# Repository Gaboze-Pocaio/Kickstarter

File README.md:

# Game Boy Zero

> Looking for a no frills multi system emulator that fits in your pocket? Look no further! This is it, Gameboy Zero - Handheld Edition!!!
>
> This project is a collaboration between  [moosepr](https://github.com/moosepr/) and  [32teeth](https://github.com/32teeth)
>
> We are **live** on [KickStarter](https://www.kickstarter.com/projects/sparky/gameboy-zero-handheld-edition)
>
> **Thank you everyone for your support.**

## Introduction

### Gameboy Zero - Handheld Edition

Raspberry Pi Zero based arcade in you pocket

### Features:

* 2.8" TFT LCD
* Gameboy button layout interface
* Raspberry Pi Zero
* Battery Charger
* Shoulder / Trigger buttons
* 60 frames per second display

### Platforms:

The boards have been tested with the following platforms:

- [x] [Emulation Station](http://www.emulationstation.org/)
- [ ] [Lakka](http://www.lakka.tv/)
- [x] [RetroPie](https://retropie.org.uk/)

Other platforms are yet to be tested.

#### Eagle CAD Library

With our project we have included a few custom Eagle CAD Libraries

* [Displays](/library/GameboyZeroHandheldDisplays.lbr)
* [Raspberry Pi Zero](/library/RPI-Zero.lbr)

#### 3D Render
* [white board with parts](https://32teeth.github.io/Gameboy-Zero-Kickstarter/?parts)
* [black board no parts](https://32teeth.github.io/Gameboy-Zero-Kickstarter/?board)
* [holiday express no parts](https://32teeth.github.io/Gameboy-Zero-Kickstarter/?holiday)

## Details

| Version               | Top                                      | Bottom                                   |
| --------------------- | ---------------------------------------- | ---------------------------------------- |
| Flat Screen           |  |  |
| Composite Board       |  |  |
| Holiday Express Board |  |  |

## Custom Silk Screen

if you plan on changin the silk design,
* use the [gameboyzero sketch](design/gameboyzero) file
* all fonts required are in the  [fonts folder](fonts/)
* export artboard (with either 'TOP' or 'BOTTOM' group active as JPG)

*converting jpg to 2 color bitmap*
```shell
# imagemagick is required brew package
$ brew install imagemagick

# convert (replace with your file names and outputs)
# ex: convert "gameboyzero-top.jpg" -depth 1 -monochrome -colors 2 "gameboyzero-top.bmp"
$ convert "[jpg to convert]" -depth 1 -monochrome -colors 2 "[bmp to output]"
```

#### Import bmp in Eagle CAD.

* File > Import > Bitmap
* Select your bitmap
* Select **only** black color
* Change scale type to *mm*
* Change scale to ***0.086** (disregard the scale in the images)*
* Place it on layer layer 21 (tPlace) or 22 (bPlace)

| Top                                     | Bottom                                   |
| --------------------------------------- | ---------------------------------------- |
|  |  |

## Plexi Case

The design for the layered plexi case are in the [case folder](/case)

*It consists of 5 layers:*
* TOP (optional for screen protection)
* SCREEN (fits over 2.8" TFT LCD)
* PI ZERO (fits around the Raspberry Pi Zero and TF4056 Module)
* BOTTOM (fits on top of the Raspberry Pi Zero)
* BATTERY (this is the layer to hold the LiPo battery in place)

## Custom Config

> If you do not plan on using the provided Raspberry Pi image, simply [download](https://retropie.org.uk/download/) the latest RetroPie pre made image for the Raspberry Pi Zero

Once you have installed RetroPie onto your SD card and mounted it on your Pi follow along with the [Installation Instructions](INSTALL.md) document provided

#### A word from our sponsor

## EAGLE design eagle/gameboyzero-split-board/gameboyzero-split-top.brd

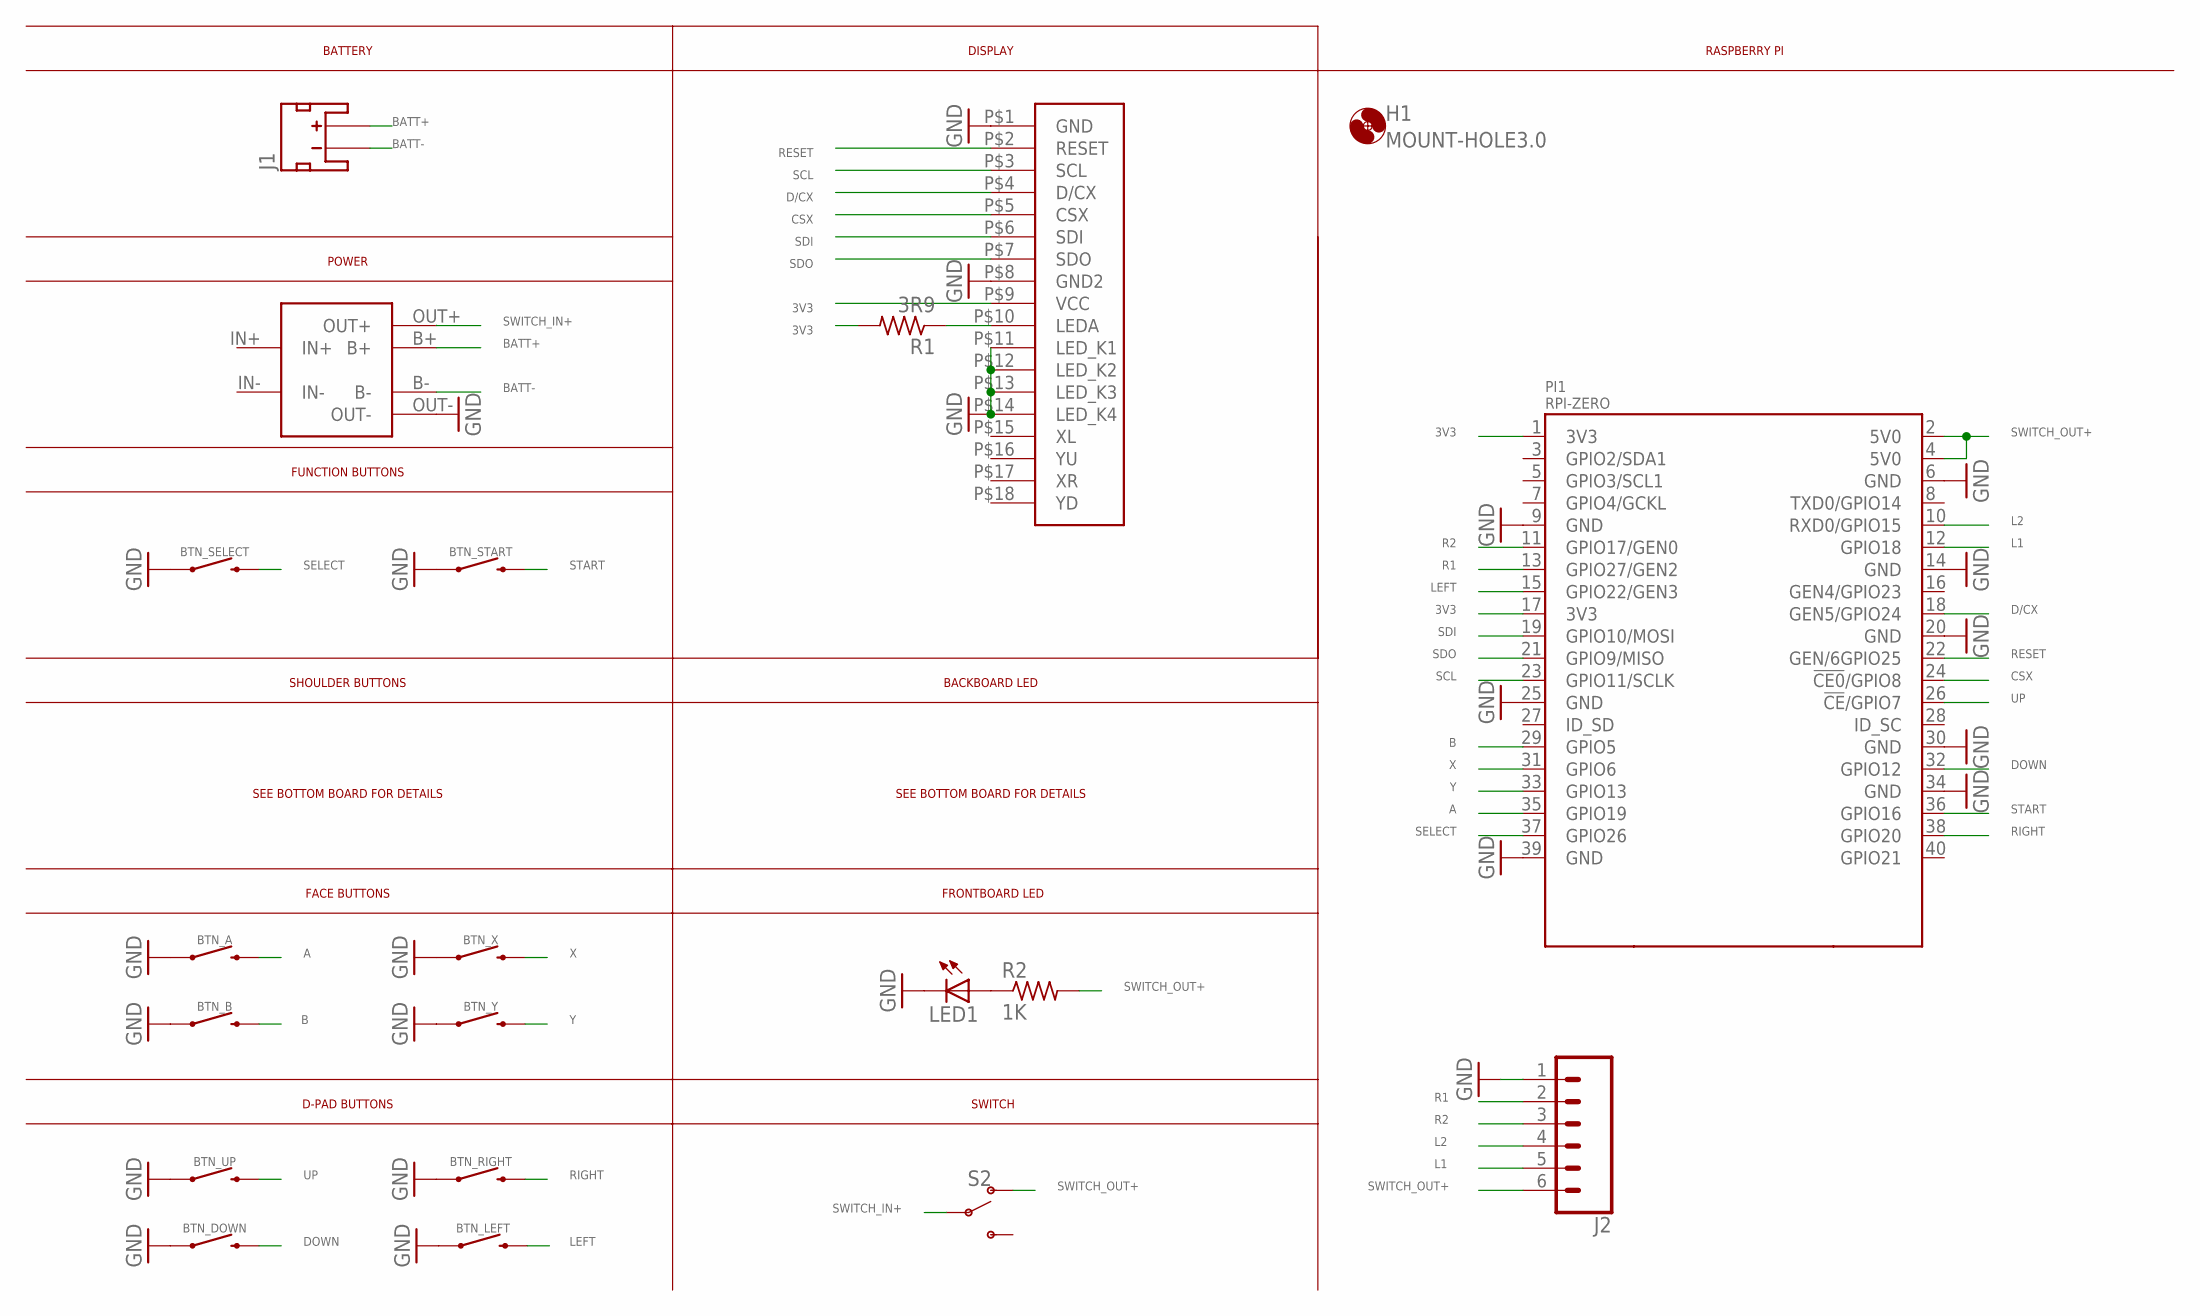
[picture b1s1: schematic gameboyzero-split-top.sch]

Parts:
BTN_A: MOMENTARY-SWITCH-SPST-SMD-12MM; TACTILE_SWITCH_SMD_12MM
BTN_B: MOMENTARY-SWITCH-SPST-SMD-12MM; TACTILE_SWITCH_SMD_12MM
BTN_DOWN: MOMENTARY-SWITCH-SPST-SMD-6.2MM-TALL; TACTILE_SWITCH_SMD_6.2MM_TALL
BTN_LEFT: MOMENTARY-SWITCH-SPST-SMD-6.2MM-TALL; TACTILE_SWITCH_SMD_6.2MM_TALL
BTN_RIGHT: MOMENTARY-SWITCH-SPST-SMD-6.2MM-TALL; TACTILE_SWITCH_SMD_6.2MM_TALL
BTN_SELECT: MOMENTARY-SWITCH-SPST-SMD-6.0X3.5MM; TACTILE_SWITCH_SMD_6.0X3.5MM
BTN_START: MOMENTARY-SWITCH-SPST-SMD-6.0X3.5MM; TACTILE_SWITCH_SMD_6.0X3.5MM
BTN_UP: MOMENTARY-SWITCH-SPST-SMD-6.2MM-TALL; TACTILE_SWITCH_SMD_6.2MM_TALL
BTN_X: MOMENTARY-SWITCH-SPST-SMD-12MM; TACTILE_SWITCH_SMD_12MM
BTN_Y: MOMENTARY-SWITCH-SPST-SMD-12MM; TACTILE_SWITCH_SMD_12MM
H1: MOUNT-HOLE3.0; 3,0
J1: JST_2MM_MALE; JST-2-SMD
J2: CONN_06SILK_FEMALE_PTH; 1X06
LED1: LEDCHIPLED_0805; CHIPLED_0805
PI1: RPI-ZERO; RASPBERRYPI_BASTELSTUBE_V13_RASPI_BOARD_B+_FULL
POWER1: 03962A
R1: 3R9; R0805
R2: 1K; R0805
S2: SWITCH-SPDT-SMD-RIGHT-ANGLE; SWITCH_SPST_SMD_A
SCREEN1: GAMEBOYZEROHANDHELDDISPLAYS-2.8

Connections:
3V3: PI1.1 (3V3), PI1.17 (3V3), R1.2, SCREEN1.P$9 (VCC)
3V3100OHM: R1.1, SCREEN1.P$10 (LEDA)
A: BTN_A.3 (2), PI1.35 (GPIO19)
B: BTN_B.3 (2), PI1.29 (GPIO5)
BATT+: J1.2 (+), POWER1.B+
BATT-: J1.1 (-), POWER1.B-
CSX: PI1.24 (!CE0!/GPIO8), SCREEN1.P$5 (CSX)
D/CX: PI1.18 (GEN5/GPIO24), SCREEN1.P$4 (D/CX)
DOWN: BTN_DOWN.B2 (2), PI1.32 (GPIO12)
GND: BTN_A.1, BTN_B.1, BTN_DOWN.A2 (1), BTN_LEFT.A2 (1), BTN_RIGHT.A2 (1), BTN_SELECT.1, BTN_START.1, BTN_UP.A2 (1), BTN_X.1, BTN_Y.1, J2.1, LED1.C, PI1.6 (GND), PI1.9 (GND), PI1.14 (GND), PI1.20 (GND), PI1.25 (GND), PI1.30 (GND), PI1.34 (GND), PI1.39 (GND), POWER1.OUT-, SCREEN1.P$1 (GND), SCREEN1.P$8 (GND2), SCREEN1.P$11 (LED_K1), SCREEN1.P$12 (LED_K2), SCREEN1.P$13 (LED_K3), SCREEN1.P$14 (LED_K4)
L1: J2.5, PI1.12 (GPIO18)
L2: J2.4, PI1.10 (RXD0/GPIO15)
LED: LED1.A, R2.1
LEFT: BTN_LEFT.B2 (2), PI1.15 (GPIO22/GEN3)
R1: J2.2, PI1.13 (GPIO27/GEN2)
R2: J2.3, PI1.11 (GPIO17/GEN0)
RESET: PI1.22 (GEN/6GPIO25), SCREEN1.P$2 (RESET)
RIGHT: BTN_RIGHT.B2 (2), PI1.38 (GPIO20)
SCL: PI1.23 (GPIO11/SCLK), SCREEN1.P$3 (SCL)
SDI: PI1.19 (GPIO10/MOSI), SCREEN1.P$6 (SDI)
SDO: PI1.21 (GPIO9/MISO), SCREEN1.P$7 (SDO)
SELECT: BTN_SELECT.2, PI1.37 (GPIO26)
START: BTN_START.2, PI1.36 (GPIO16)
SWITCH_IN+: POWER1.OUT+, S2.2
SWITCH_OUT+: J2.6, PI1.2 (5V0), PI1.4 (5V0), R2.2, S2.1 (O)
UP: BTN_UP.B2 (2), PI1.26 (!CE!/GPIO7)
X: BTN_X.3 (2), PI1.31 (GPIO6)
Y: BTN_Y.3 (2), PI1.33 (GPIO13)

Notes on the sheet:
D-PAD BUTTONS
FACE BUTTONS
SHOULDER BUTTONS
FUNCTION BUTTONS
POWER
BATTERY
SWITCH
FRONTBOARD LED
DISPLAY
RASPBERRY PI
BACKBOARD LED
SEE BOTTOM BOARD FOR DETAILS

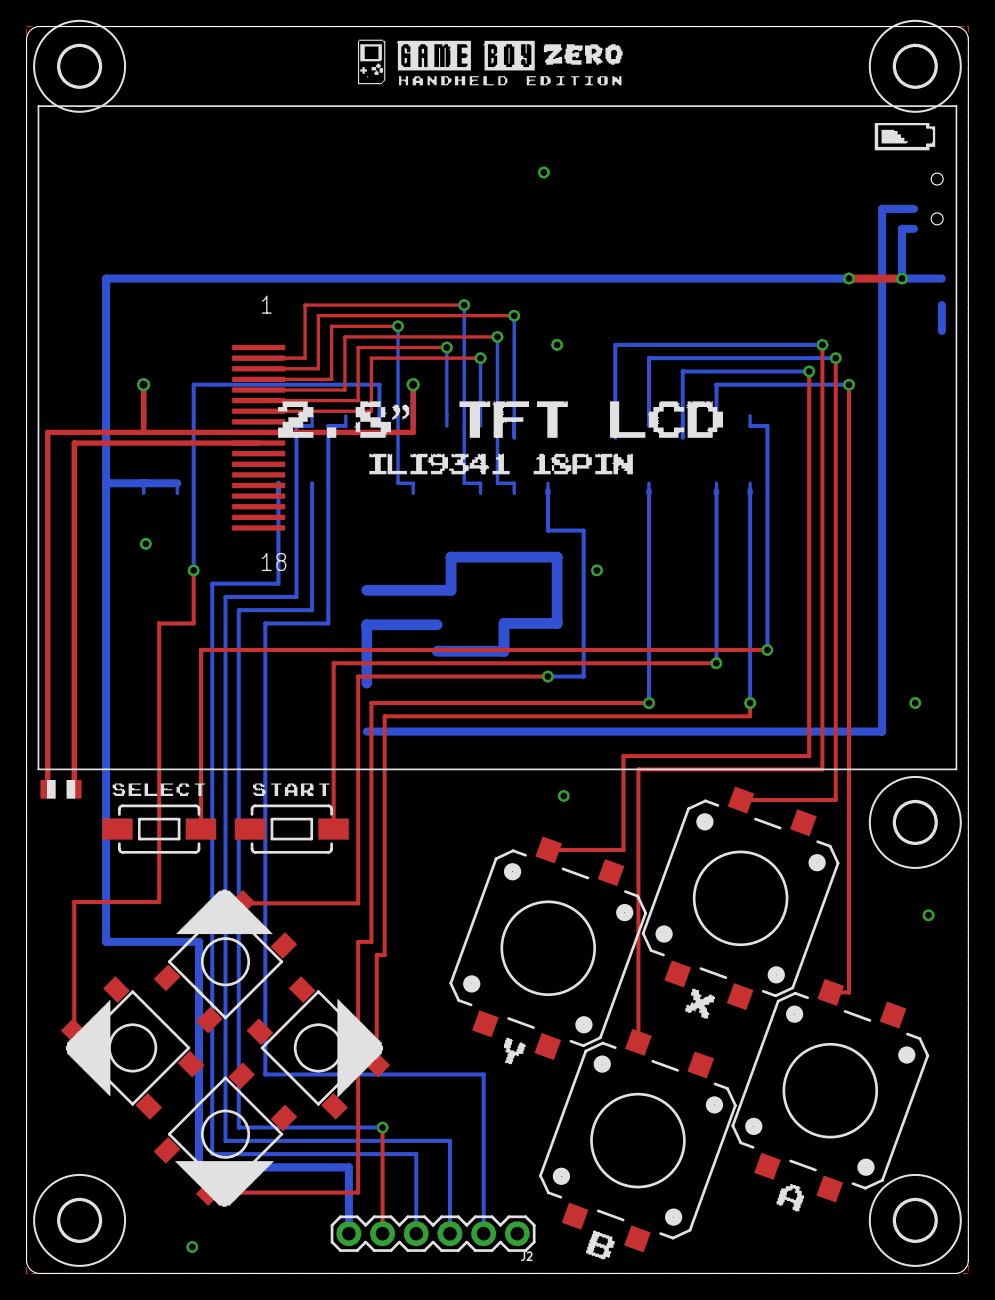
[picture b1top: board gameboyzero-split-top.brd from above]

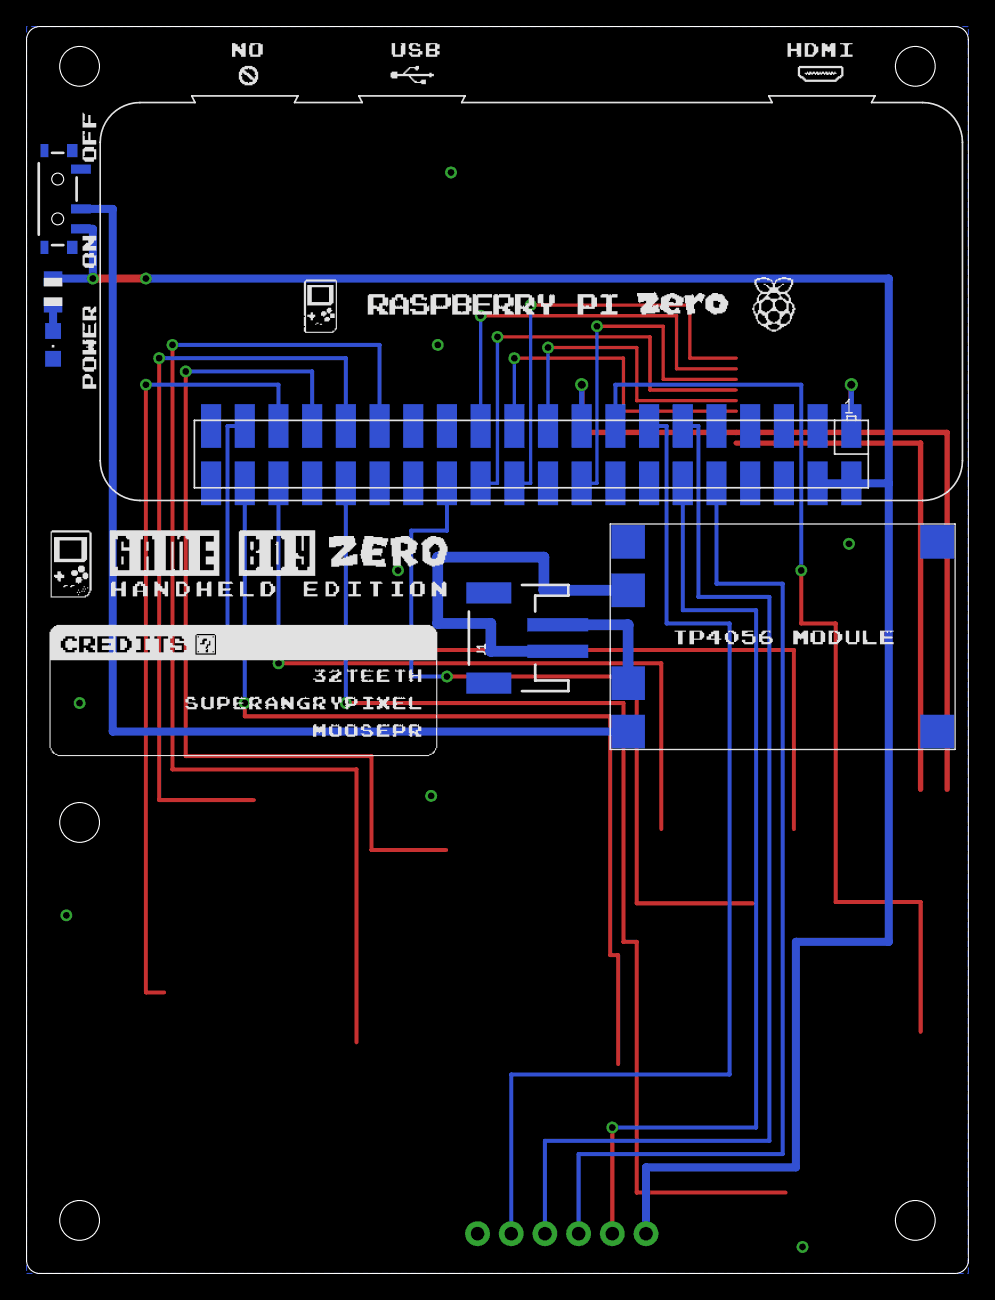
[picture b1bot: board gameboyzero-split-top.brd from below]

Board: 2 copper layers, 71.0 x 94.0 mm, 24 parts (6 on the bottom side), 28 nets.

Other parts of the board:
H2, H3, H4, H5: MOUNT-HOLE2.8; 3,0

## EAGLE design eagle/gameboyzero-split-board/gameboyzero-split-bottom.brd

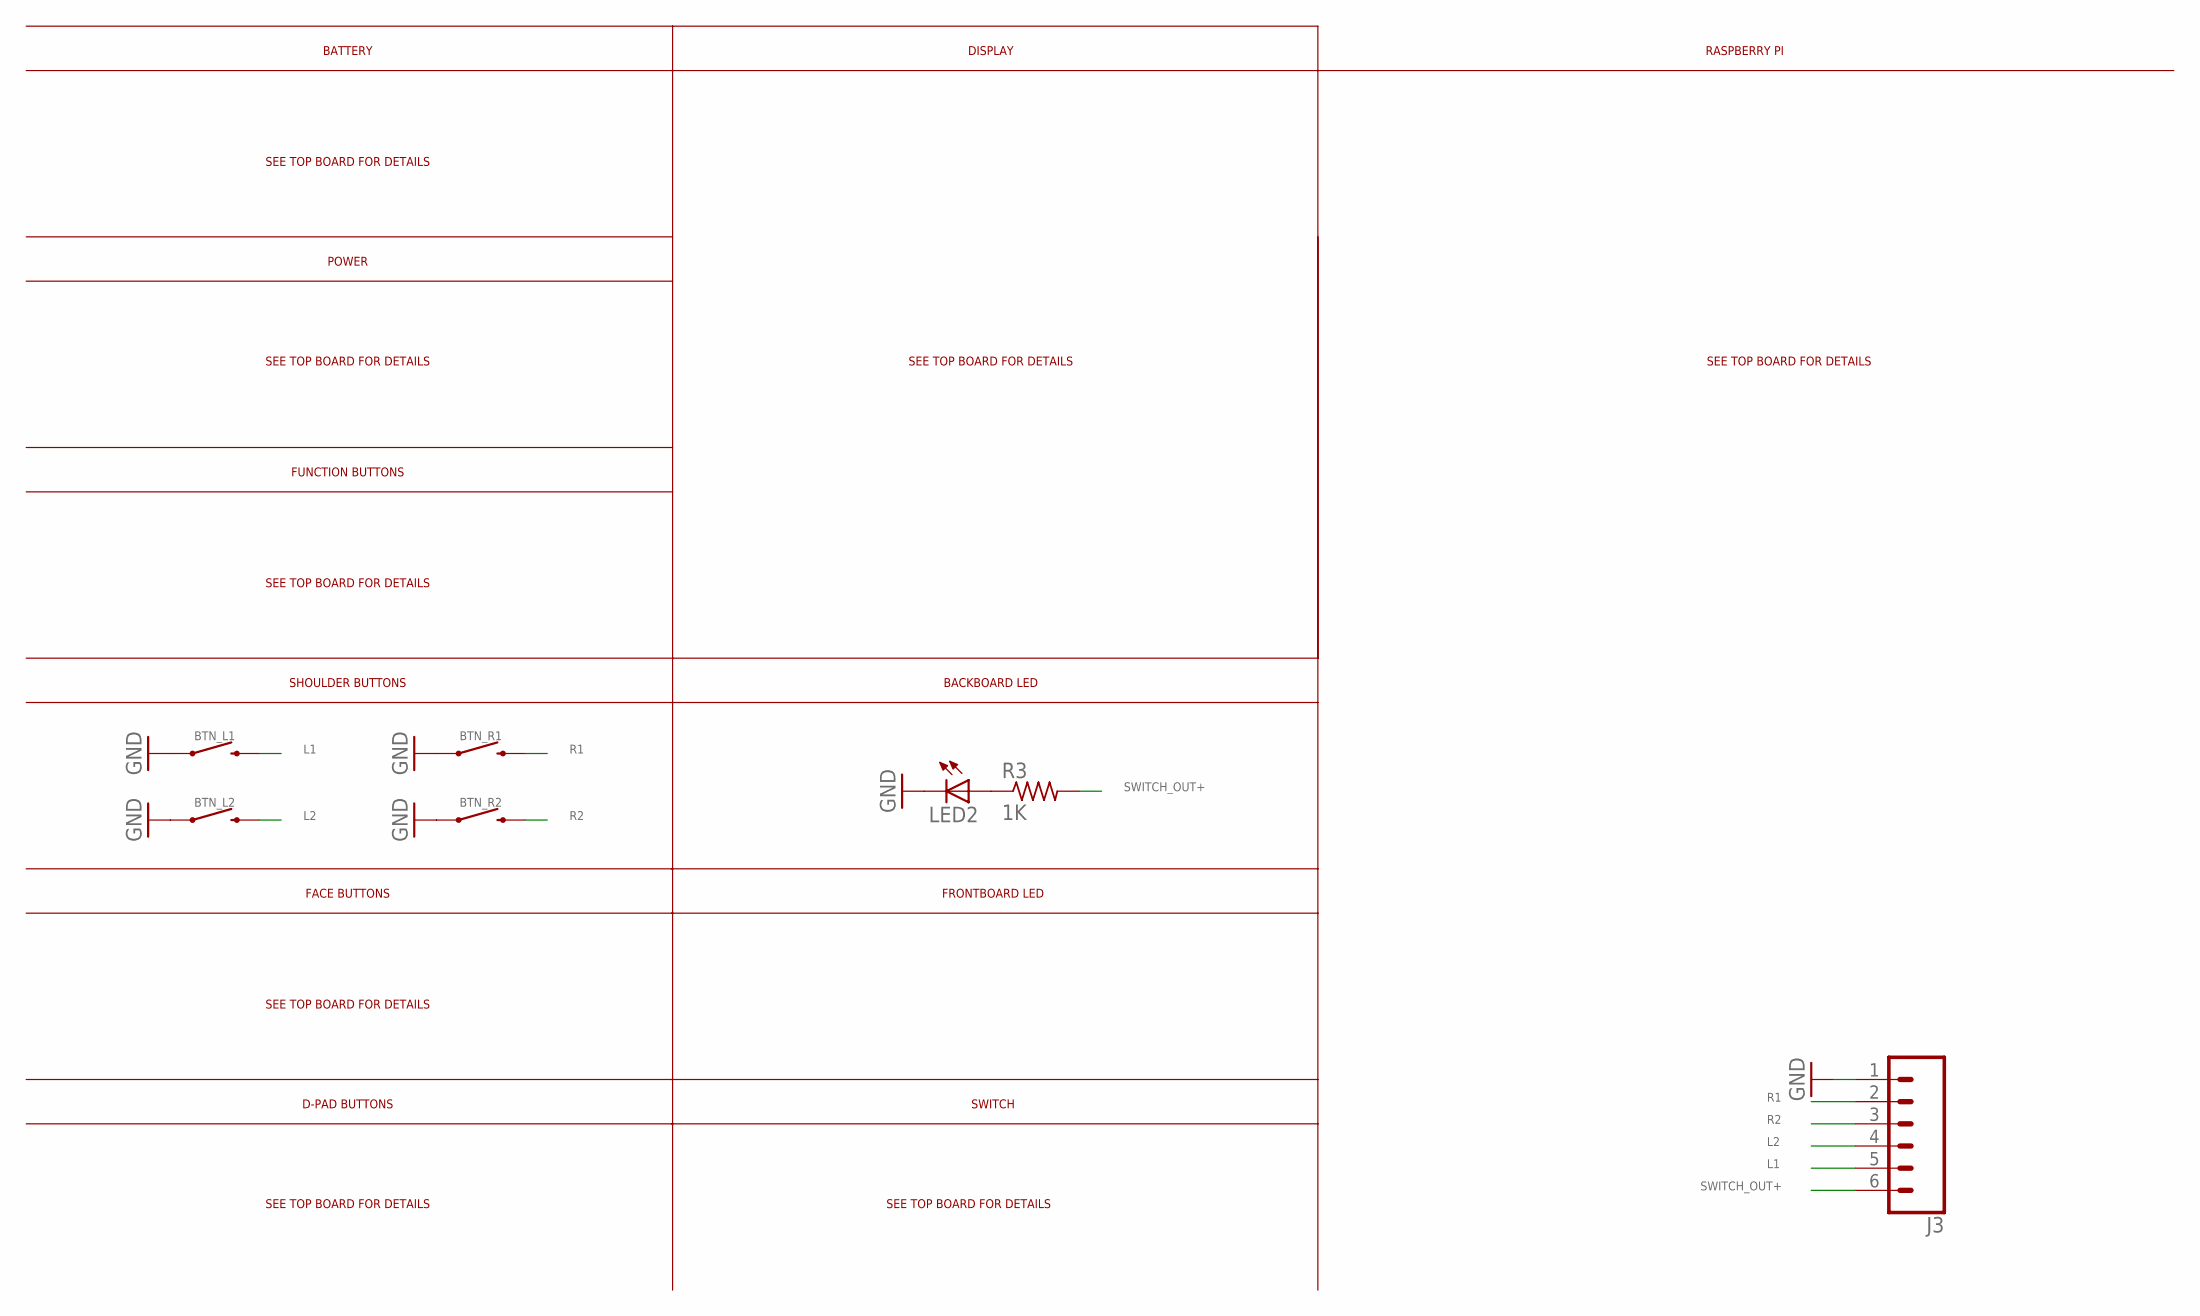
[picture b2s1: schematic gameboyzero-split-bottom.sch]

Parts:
BTN_L1, BTN_L2: MOMENTARY-SWITCH-SPST-SMD-12MM; TACTILE_SWITCH_SMD_12MM
BTN_R1, BTN_R2: MOMENTARY-SWITCH-SPST-SMD-12MM; TACTILE_SWITCH_SMD_12MM
J3: CONN_06SILK_FEMALE_PTH; 1X06
LED2: LEDCHIPLED_0805; CHIPLED_0805
R3: 1K; R0805

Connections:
GND: BTN_L1.1, BTN_L2.1, BTN_R1.1, BTN_R2.1, J3.1, LED2.C
L1: BTN_L1.3 (2), J3.5
L2: BTN_L2.3 (2), J3.4
LED1: LED2.A, R3.1
R1: BTN_R1.3 (2), J3.2
R2: BTN_R2.3 (2), J3.3
SWITCH_OUT+: J3.6, R3.2

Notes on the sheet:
D-PAD BUTTONS
FACE BUTTONS
SHOULDER BUTTONS
FUNCTION BUTTONS
POWER
BATTERY
SWITCH
FRONTBOARD LED
DISPLAY
RASPBERRY PI
BACKBOARD LED
SEE TOP BOARD FOR DETAILS

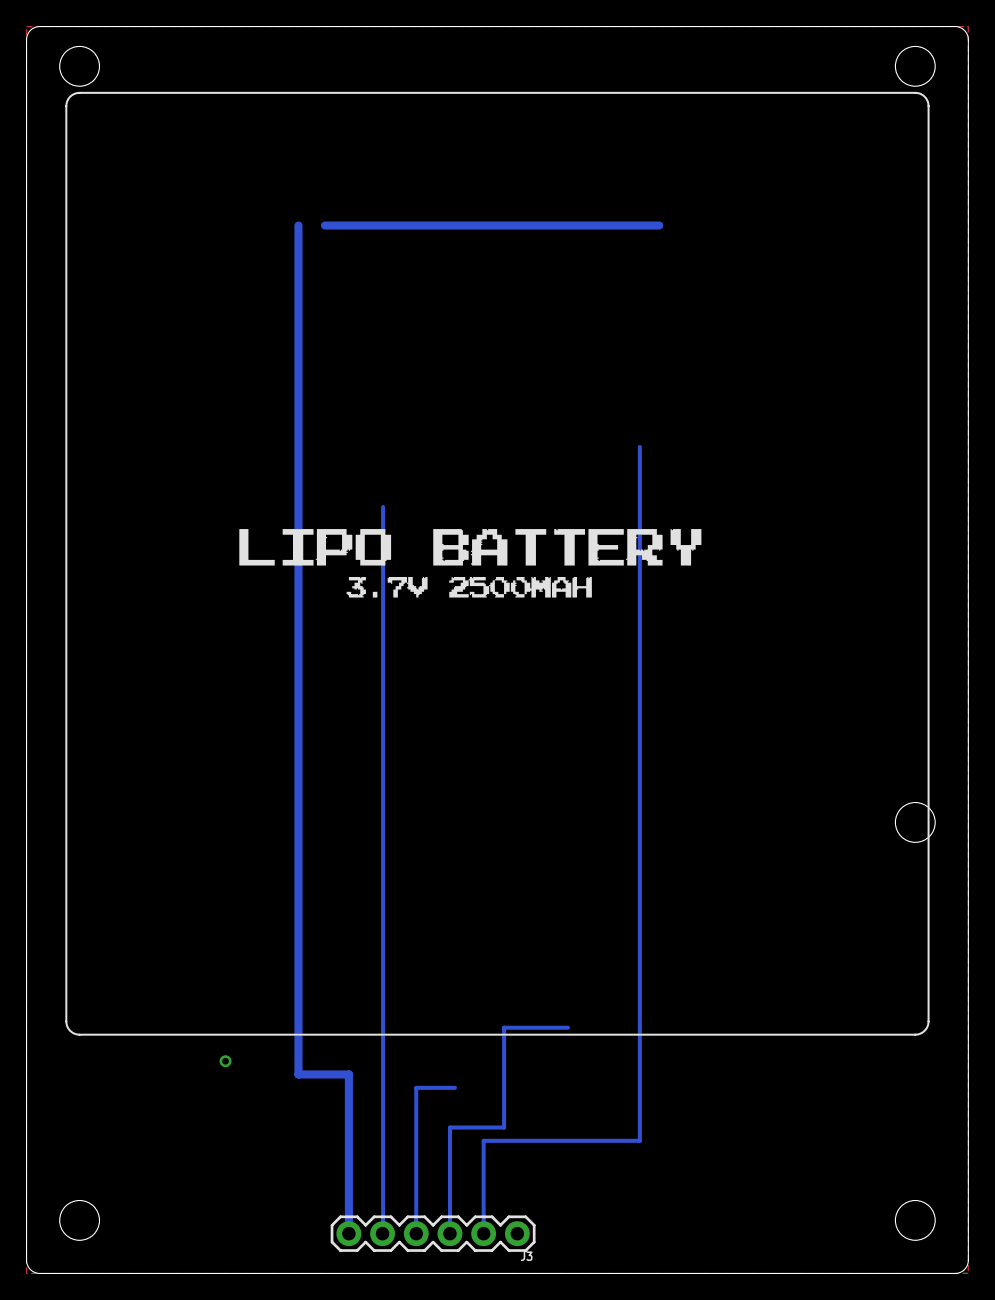
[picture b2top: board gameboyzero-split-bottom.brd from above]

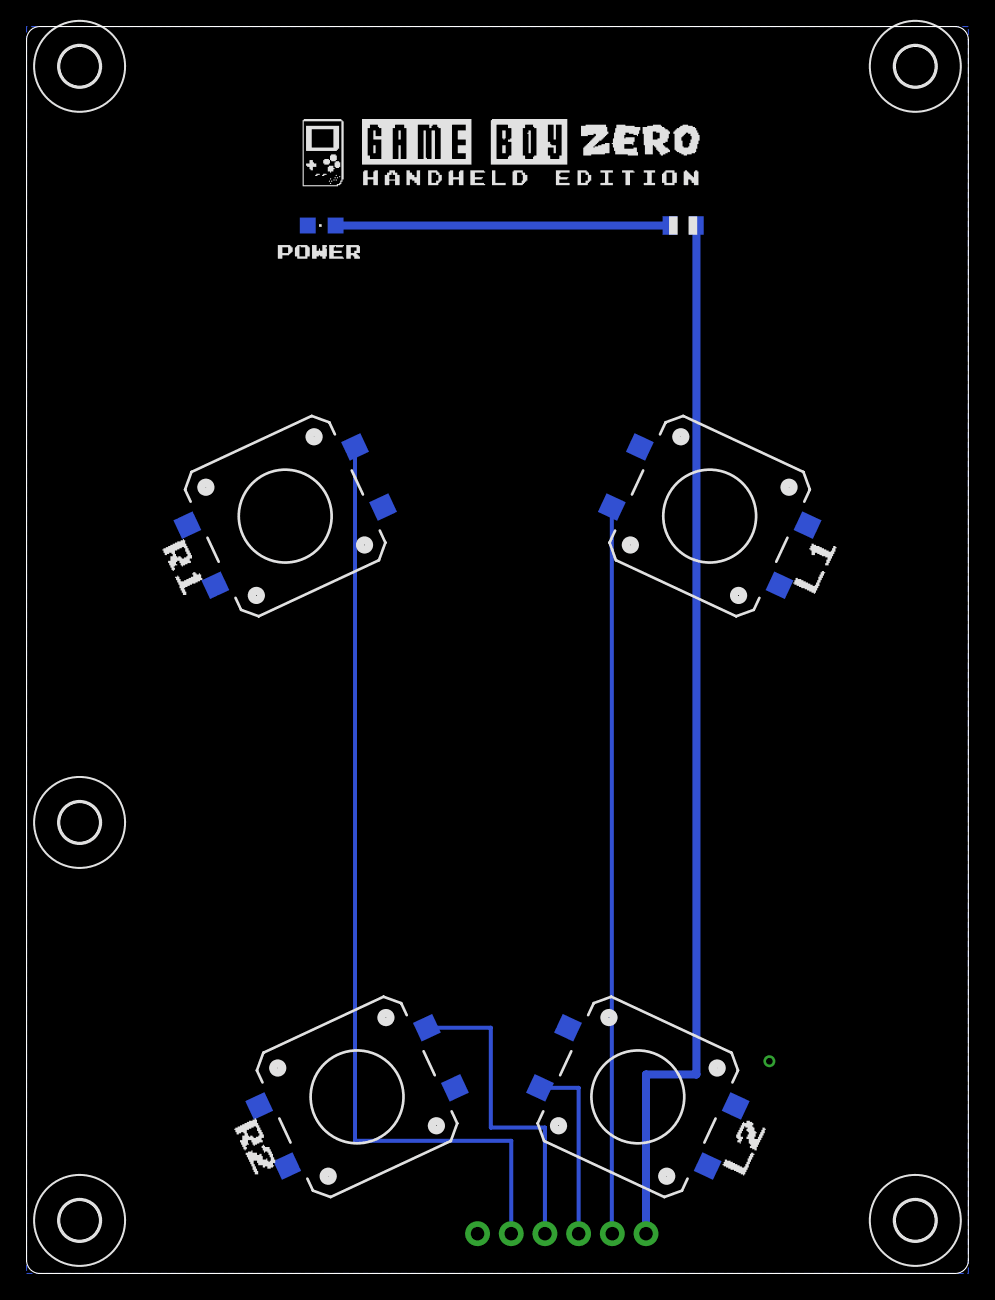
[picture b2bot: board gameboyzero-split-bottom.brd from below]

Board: 2 copper layers, 71.0 x 94.0 mm, 12 parts (11 on the bottom side), 7 nets.

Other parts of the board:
H6, H7, H8, H9, H10: MOUNT-HOLE2.8; 3,0

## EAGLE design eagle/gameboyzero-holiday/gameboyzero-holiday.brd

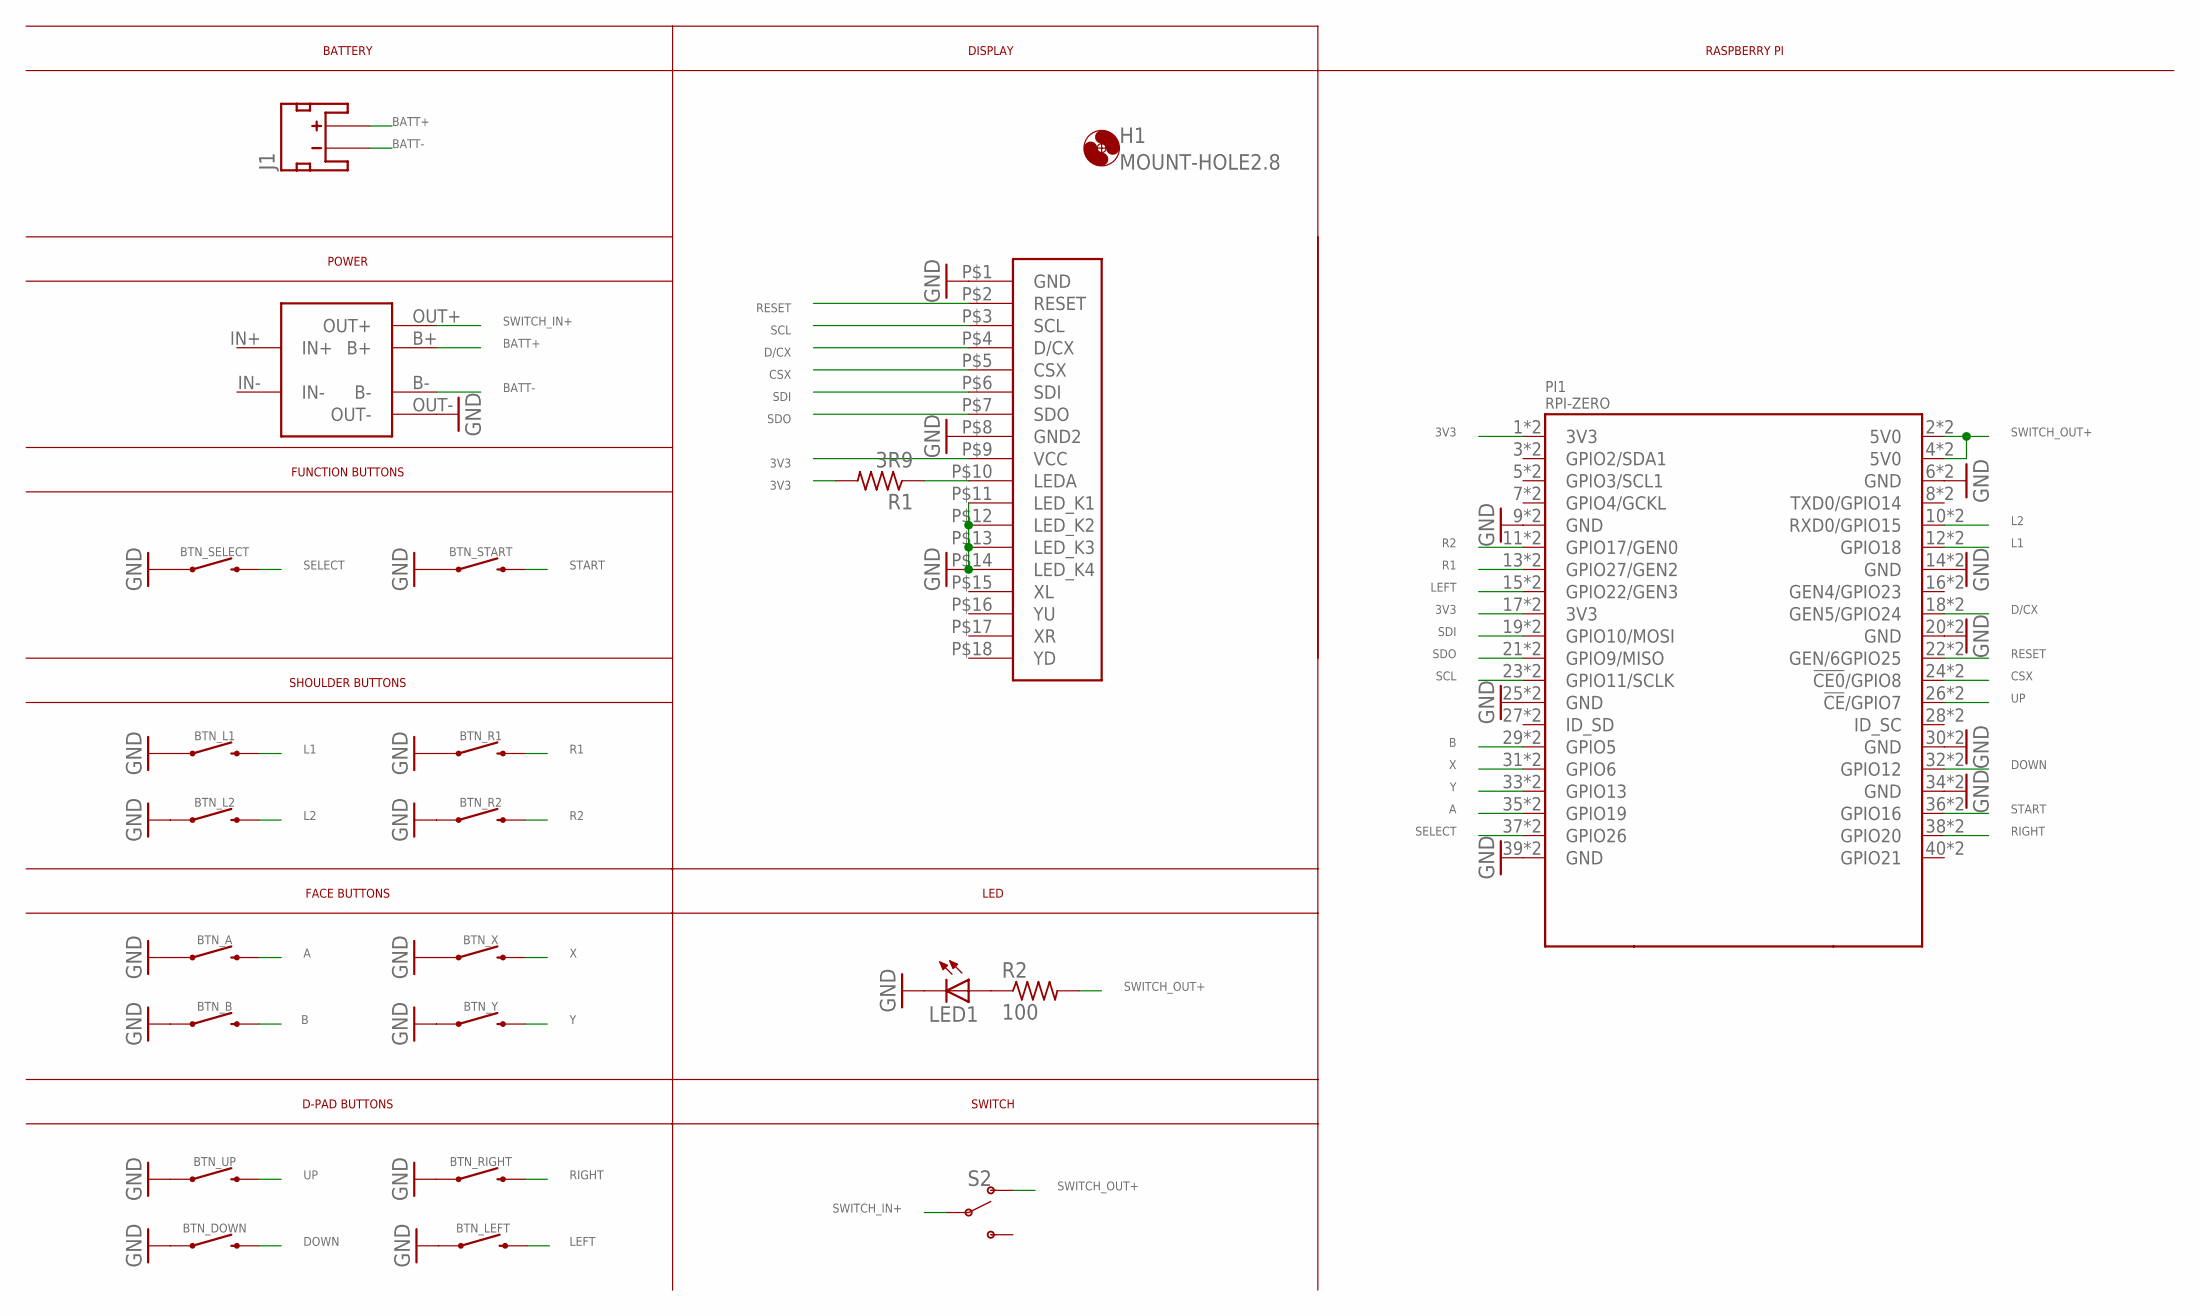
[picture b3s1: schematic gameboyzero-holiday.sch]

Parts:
BTN_A: MOMENTARY-SWITCH-SPST-SMD-12MM; TACTILE_SWITCH_SMD_12MM
BTN_B: MOMENTARY-SWITCH-SPST-SMD-12MM; TACTILE_SWITCH_SMD_12MM
BTN_DOWN: MOMENTARY-SWITCH-SPST-SMD-6.2MM-TALL; TACTILE_SWITCH_SMD_6.2MM_TALL
BTN_L1, BTN_L2: MOMENTARY-SWITCH-SPST-SMD-12MM; TACTILE_SWITCH_SMD_12MM
BTN_LEFT: MOMENTARY-SWITCH-SPST-SMD-6.2MM-TALL; TACTILE_SWITCH_SMD_6.2MM_TALL
BTN_R1, BTN_R2: MOMENTARY-SWITCH-SPST-SMD-12MM; TACTILE_SWITCH_SMD_12MM
BTN_RIGHT: MOMENTARY-SWITCH-SPST-SMD-6.2MM-TALL; TACTILE_SWITCH_SMD_6.2MM_TALL
BTN_SELECT: MOMENTARY-SWITCH-SPST-SMD-6.0X3.5MM; TACTILE_SWITCH_SMD_6.0X3.5MM
BTN_START: MOMENTARY-SWITCH-SPST-SMD-6.0X3.5MM; TACTILE_SWITCH_SMD_6.0X3.5MM
BTN_UP: MOMENTARY-SWITCH-SPST-SMD-6.2MM-TALL; TACTILE_SWITCH_SMD_6.2MM_TALL
BTN_X: MOMENTARY-SWITCH-SPST-SMD-12MM; TACTILE_SWITCH_SMD_12MM
BTN_Y: MOMENTARY-SWITCH-SPST-SMD-12MM; TACTILE_SWITCH_SMD_12MM
H1: MOUNT-HOLE2.8; 2,8
J1: JST_2MM_MALE; JST-2-SMD
LED1: LEDCHIPLED_0805; CHIPLED_0805
PI1: RPI-ZERO; RASPBERRYPI_BASTELSTUBE_V13_RASPI_BOARD_B+_FULL
POWER1: 03962A
R1: 3R9; R0805
R2: 100; R0805
S2: SWITCH-SPDT-SMD-RIGHT-ANGLE; SWITCH_SPST_SMD_A
SCREEN1: GAMEBOYZEROHANDHELDDISPLAYS-2.8

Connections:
3V3: PI1.1 (3V3), PI1.17 (3V3), PI1.41 (3V3), PI1.57 (3V3), R1.2, SCREEN1.P$9 (VCC)
3V3100OHM: R1.1, SCREEN1.P$10 (LEDA)
A: BTN_A.3 (2), PI1.35 (GPIO19), PI1.75 (GPIO19)
B: BTN_B.3 (2), PI1.29 (GPIO5), PI1.69 (GPIO5)
BATT+: J1.2 (+), POWER1.B+
BATT-: J1.1 (-), POWER1.B-
CSX: PI1.24 (!CE0!/GPIO8), PI1.64 (!CE0!/GPIO8), SCREEN1.P$5 (CSX)
D/CX: PI1.18 (GEN5/GPIO24), PI1.58 (GEN5/GPIO24), SCREEN1.P$4 (D/CX)
DOWN: BTN_DOWN.B2 (2), PI1.32 (GPIO12), PI1.72 (GPIO12)
GND: BTN_A.1, BTN_B.1, BTN_DOWN.A2 (1), BTN_L1.1, BTN_L2.1, BTN_LEFT.A2 (1), BTN_R1.1, BTN_R2.1, BTN_RIGHT.A2 (1), BTN_SELECT.1, BTN_START.1, BTN_UP.A2 (1), BTN_X.1, BTN_Y.1, LED1.C, PI1.6 (GND), PI1.9 (GND), PI1.14 (GND), PI1.20 (GND), PI1.25 (GND), PI1.30 (GND), PI1.34 (GND), PI1.39 (GND), PI1.46 (GND), PI1.49 (GND), PI1.54 (GND), PI1.60 (GND), PI1.65 (GND), PI1.70 (GND), PI1.74 (GND), PI1.79 (GND), POWER1.OUT-, SCREEN1.P$1 (GND), SCREEN1.P$8 (GND2), SCREEN1.P$11 (LED_K1), SCREEN1.P$12 (LED_K2), SCREEN1.P$13 (LED_K3), SCREEN1.P$14 (LED_K4)
L1: BTN_L1.3 (2), PI1.12 (GPIO18), PI1.52 (GPIO18)
L2: BTN_L2.3 (2), PI1.10 (RXD0/GPIO15), PI1.50 (RXD0/GPIO15)
LED: LED1.A, R2.1
LEFT: BTN_LEFT.B2 (2), PI1.15 (GPIO22/GEN3), PI1.55 (GPIO22/GEN3)
R1: BTN_R1.3 (2), PI1.13 (GPIO27/GEN2), PI1.53 (GPIO27/GEN2)
R2: BTN_R2.3 (2), PI1.11 (GPIO17/GEN0), PI1.51 (GPIO17/GEN0)
RESET: PI1.22 (GEN/6GPIO25), PI1.62 (GEN/6GPIO25), SCREEN1.P$2 (RESET)
RIGHT: BTN_RIGHT.B2 (2), PI1.38 (GPIO20), PI1.78 (GPIO20)
SCL: PI1.23 (GPIO11/SCLK), PI1.63 (GPIO11/SCLK), SCREEN1.P$3 (SCL)
SDI: PI1.19 (GPIO10/MOSI), PI1.59 (GPIO10/MOSI), SCREEN1.P$6 (SDI)
SDO: PI1.21 (GPIO9/MISO), PI1.61 (GPIO9/MISO), SCREEN1.P$7 (SDO)
SELECT: BTN_SELECT.2, PI1.37 (GPIO26), PI1.77 (GPIO26)
START: BTN_START.2, PI1.36 (GPIO16), PI1.76 (GPIO16)
SWITCH_IN+: POWER1.OUT+, S2.2
SWITCH_OUT+: PI1.2 (5V0), PI1.4 (5V0), PI1.42 (5V0), PI1.44 (5V0), R2.2, S2.1 (O)
UP: BTN_UP.B2 (2), PI1.26 (!CE!/GPIO7), PI1.66 (!CE!/GPIO7)
X: BTN_X.3 (2), PI1.31 (GPIO6), PI1.71 (GPIO6)
Y: BTN_Y.3 (2), PI1.33 (GPIO13), PI1.73 (GPIO13)

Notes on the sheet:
D-PAD BUTTONS
FACE BUTTONS
SHOULDER BUTTONS
FUNCTION BUTTONS
POWER
BATTERY
SWITCH
LED
DISPLAY
RASPBERRY PI

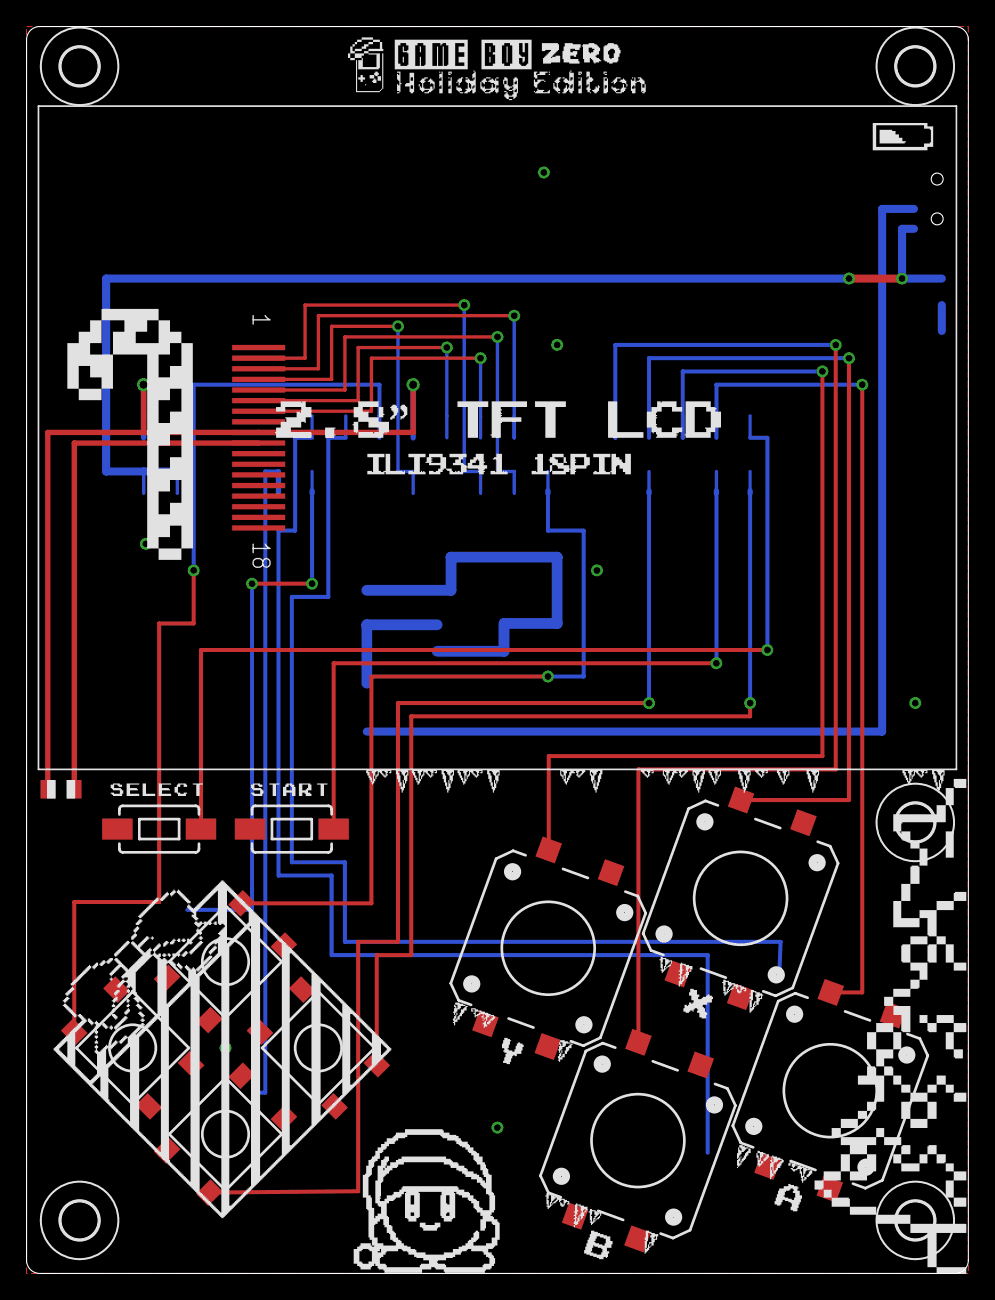
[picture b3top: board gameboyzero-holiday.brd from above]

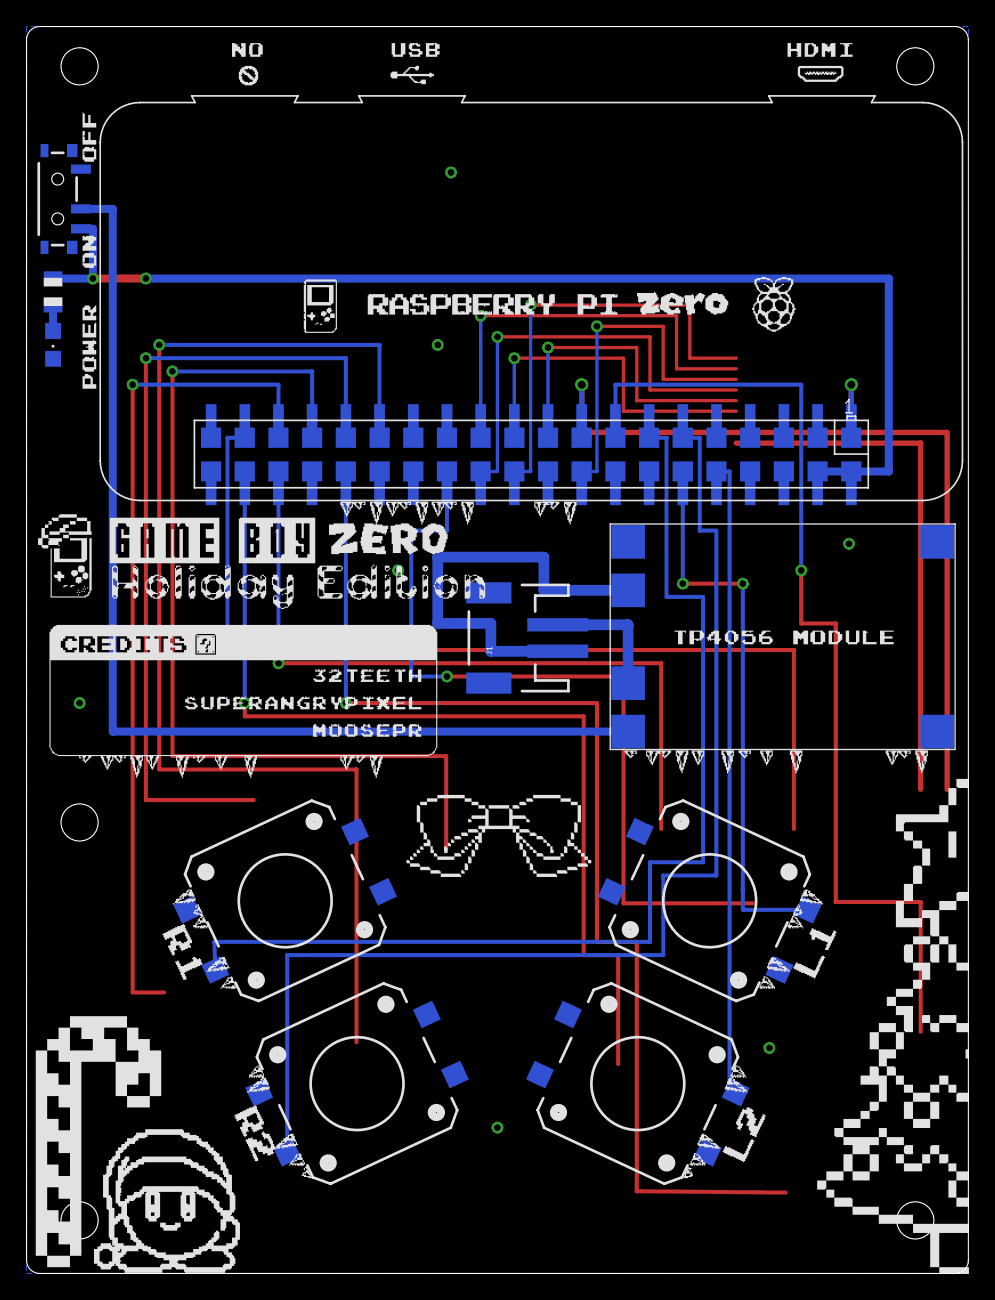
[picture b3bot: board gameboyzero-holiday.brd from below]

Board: 2 copper layers, 71.0 x 94.0 mm, 27 parts (10 on the bottom side), 28 nets.

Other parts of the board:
H2, H3, H4, H5: MOUNT-HOLE2.8; 2,8

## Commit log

2017-10-10 Inital commit post KickStarter launch
2017-10-10 Updated Case Directory
2017-10-10 Updated BOM Directory
2017-10-10 Added License
2017-10-10 Removed Copyrights and Trademarks
2017-10-11 New Silk and New Case files
2017-10-11 Wed 11 Oct 2017 16:52:53 EDT
2017-10-11 Wed 11 Oct 2017 17:09:49 EDT
2017-10-11 Wed 11 Oct 2017 17:13:01 EDT
2017-10-12 Thu 12 Oct 2017 11:18:29 EDT
2017-10-13 Fri 13 Oct 2017 13:47:56 EDT
2017-10-13 Fri 13 Oct 2017 16:15:10 EDT
2017-10-17 Tue 17 Oct 2017 18:00:43 EDT updated gerbers
2017-10-18 Wed 18 Oct 2017 19:37:03 EDT updated gerbers
2017-10-19 Thu 19 Oct 2017 10:10:47 EDT - holiday express board released
2017-10-19 Thu 19 Oct 2017 10:17:15 EDT - holiday express board released
2017-10-23 Mon 23 Oct 2017 13:27:00 EDT - holiday express board released
2017-10-25 Wed 25 Oct 2017 09:07:01 EDT - holiday express board released
2017-10-25 Wed 25 Oct 2017 09:57:53 EDT - holiday express board released
2017-10-26 Thu 26 Oct 2017 08:34:56 EDT - holiday express board released
2017-10-27 Fri 27 Oct 2017 10:05:30 EDT - holiday express board released
2017-10-30 Mon 30 Oct 2017 11:48:34 EDT - new case
2017-10-30 Mon 30 Oct 2017 18:03:52 EDT - new case
2017-10-31 last minute fixes before production
2017-10-31 Tue 31 Oct 2017 16:24:41 EDT
2017-11-03 Fri 3 Nov 2017 16:21:28 EDT
2017-11-07 Tue 7 Nov 2017 15:07:46 EST
2017-11-07 Tue 7 Nov 2017 15:28:11 EST
2017-11-07 Tue 7 Nov 2017 15:29:14 EST
2017-11-08 Tue Nov 7 23:54:05 EST 2017
2017-11-08 Tue Nov 7 23:58:46 EST 2017
2017-11-08 Wed 8 Nov 2017 12:24:01 EST
2017-11-08 Wed 8 Nov 2017 16:26:35 EST
2017-11-11 Sat 11 Nov 2017 12:27:48 EST
2017-11-11 added new splash screen
2017-11-14 Tue 14 Nov 2017 17:21:10 EST
2017-11-16 install.m dfix
2017-11-21 Mon 20 Nov 2017 21:17:25 EST
2017-11-21 Mon 20 Nov 2017 21:21:54 EST
2017-11-21 Tue 21 Nov 2017 08:23:09 EST
2017-11-23 Thu 23 Nov 2017 15:30:06 EST
2017-11-23 Thu 23 Nov 2017 16:25:19 EST
2017-11-23 Thu 23 Nov 2017 17:20:47 EST
2017-11-24 Fri 24 Nov 2017 10:30:35 EST
2017-11-24 Fri 24 Nov 2017 11:23:44 EST
2017-11-24 Fri 24 Nov 2017 17:05:07 EST
2017-11-27 Mon 27 Nov 2017 11:39:46 EST
2017-11-28 Tue 28 Nov 2017 18:37:52 EST
2017-12-01 Fri 1 Dec 2017 08:32:23 CST
2017-12-06 Wed 6 Dec 2017 14:49:20 EST
2017-12-11 Mon 11 Dec 2017 15:37:02 EST
2017-12-12 Mon Dec 11 23:49:02 EST 2017
2017-12-12 Tue 12 Dec 2017 14:39:35 EST - edited retrogame.cfg with RIGHTSHIFT for Select button
2017-12-17 Sun 17 Dec 2017 11:46:54 EST - edited retrogame.cfg with RIGHTSHIFT for Select button
2017-12-20 Wed Dec 20 17:22:54 EST 2017
2018-01-02 Tue 2 Jan 2018 16:26:20 EST
2018-01-03 Wed 3 Jan 2018 12:40:18 EST
2018-01-03 Wed 3 Jan 2018 12:56:02 EST
2018-01-03 added gerbers
2018-01-04 remove codesponsor
2018-01-12 Fri 12 Jan 2018 17:10:25 EST
2018-01-25 simplified plexi
2018-01-25 update istall
2018-02-14 Wed 14 Feb 2018 12:34:53 EST
2018-02-22 Thu 22 Feb 2018 09:08:23 EST
2018-02-22 Thu 22 Feb 2018 09:10:33 EST
2018-02-22 Thu 22 Feb 2018 09:11:24 EST
2018-03-05 Mon 5 Mar 2018 14:09:31 EST

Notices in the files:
parts and their libraries:
SparkFun-Switches: Licensing: Creative Commons ShareAlike 4.0 International - https://creativecommons.org/licenses/by-sa/4.0
